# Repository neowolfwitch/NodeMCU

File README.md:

# NodeMCU
 D1-Mini, ESP-16, ESP-32 etc.

Please read the license terms carefully, as the author disclaims all liability for everything included here.

***This software is distributed AS-IS without support.*** 

I have a "day job" and just don't have time to provide technical support for this stuff. There are a lot of resources available online for xLights, FPP, Arduino, C, PHP, etc, and my code is well-commented. Please do not attempt to compile or use anything here unless you have a high level of comfort with the tools involved.

Many resources can be found here: https://lunardenlights.com/pixel-resources/

...and here: https://lunardenlights.com/terminology/

I'm happy to respond to feedback, suggestions, and simple questions as I have time, but I can't support xLights, FPP, Arduino IDE, or Visual Studio Code.

Thanks!

Wolf I. Butler

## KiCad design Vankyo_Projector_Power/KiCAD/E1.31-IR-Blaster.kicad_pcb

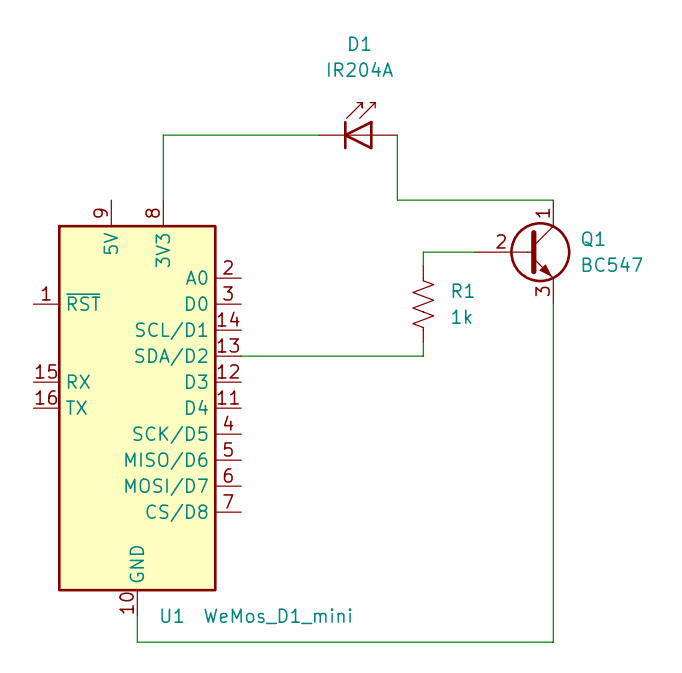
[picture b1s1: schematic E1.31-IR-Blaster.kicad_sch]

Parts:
D1: IR204A; LED_D3.0mm_IRBlack
Q1: BC547; TO-92_Inline
R1: 1k; R_Axial_DIN0204_L3.6mm_D1.6mm_P7.62mm_Horizontal
U1: WeMos_D1_mini; WEMOS_D1_mini_light

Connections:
unnamed: D1.1 (K), U1.8 (3V3)
unnamed: D1.2 (A), Q1.1 (C)
unnamed: Q1.2 (B), R1.1
unnamed: Q1.3 (E), U1.10 (GND)
unnamed: R1.2, U1.13 (SDA/D2)

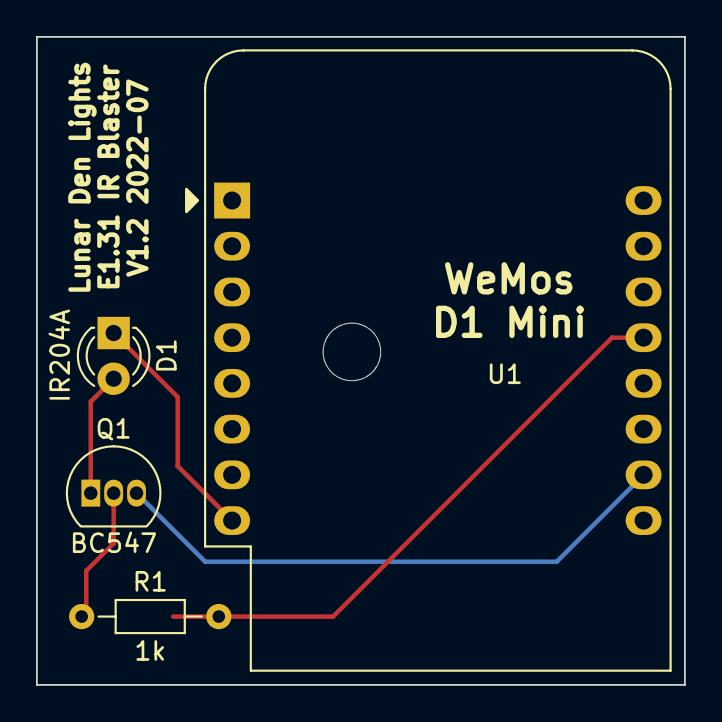
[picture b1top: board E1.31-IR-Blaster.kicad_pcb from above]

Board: 2 copper layers, 36.0 x 36.0 mm, 4 parts (0 on the bottom side), 5 nets.

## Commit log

2022-01-12 Cleanup
2022-07-13 Adding new Web code
2022-08-01 Update D1_Relay_Controller.ino
    Updated notes.
2022-08-01 Update D1_Relay_Controller.ino
    Added more comments to help new users, in particular with fixed IP and Multicast/Unicast.
